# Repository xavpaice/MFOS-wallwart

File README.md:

# MFOS-wallwart

Slightly updated MFOS wallwart power supply for Eurorack, adding a +5V rail.

V0.1 dev version

This schematic and PCB is written using Kicad, v6.0.2

For the original circuit, see http://musicfromouterspace.com/analogsynth_new/WALLWARTSUPPLY/WALLWARTSUPPLY.php.

Though I have used insanely thick traces, the actual rating of the circuit with
stated components is about 1A total.  If you need more, consider something more
expensive.

The information in this repository is provided in good faith but no
responsibility is accepted for the accuracy or suitability for any purpose; you
use it entirely at your own risk.

Please report errors and omissions at
https://github.com/xavpaice/MFOS-wallwart/issues.

Misuse of electronics can result in nasty things like death, or, worse, fried
Eurorack modules.  Please take care.  Remember to only chew on lead free diodes.

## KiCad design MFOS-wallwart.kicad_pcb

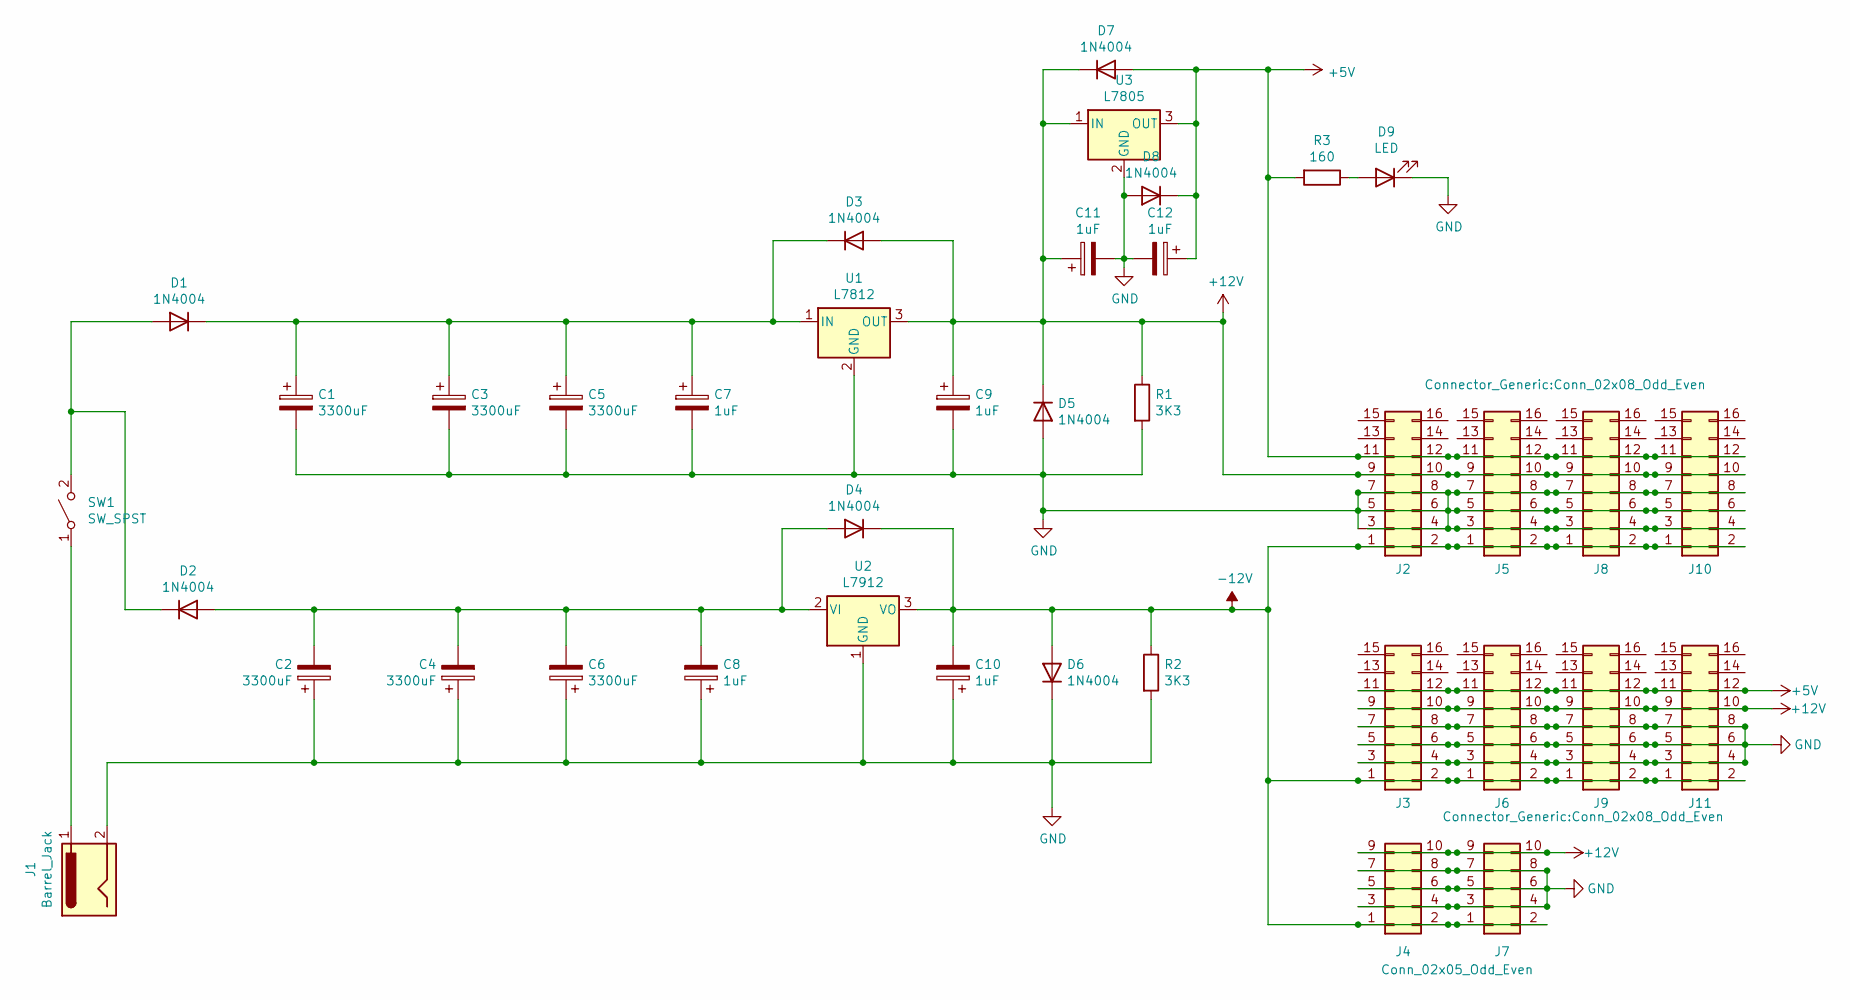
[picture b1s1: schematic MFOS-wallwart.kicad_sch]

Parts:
C1, C2, C3, C4, C5, C6: 3300uF; CP_Radial_D18.0mm_P7.50mm
C7, C8, C9, C10, C11, C12: 1uF; CP_Radial_D6.3mm_P2.50mm
D1, D2, D3, D4, D5, D6, D7, D8: 1N4004; D_DO-41_SOD81_P10.16mm_Horizontal
D9: LED; PinHeader_1x02_P2.54mm_Vertical
J1: Barrel_Jack; PinHeader_1x02_P2.54mm_Vertical
J2, J3, J5, J6, J8, J9, J10, J11: Connector_Generic:Conn_02x08_Odd_Even; IDC-Header_2x08_P2.54mm_Vertical
J4, J7: Conn_02x05_Odd_Even; PinHeader_2x05_P2.54mm_Vertical
R1, R2: 3K3; R_Axial_DIN0207_L6.3mm_D2.5mm_P10.16mm_Horizontal
R3: 160; R_Axial_DIN0207_L6.3mm_D2.5mm_P10.16mm_Horizontal
SW1: SW_SPST; PinHeader_1x02_P2.54mm_Vertical
U1: L7812; TO-220-3_Vertical
U2: L7912; TO-220-3_Vertical
U3: L7805; TO-220-3_Vertical

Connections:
+5V: C12.1, D7.2 (A), D8.1 (K), J2.11, J2.12, J3.11, J3.12, J5.11, J5.12, J6.11, J6.12, J8.11, J8.12, J9.11, J9.12, J10.11, J10.12, J11.11, J11.12, R3.2, U3.3 (OUT)
+12V: C9.1, C11.1, D3.2 (A), D5.1 (K), D7.1 (K), J2.9, J2.10, J3.9, J3.10, J4.9, J4.10, J5.9, J5.10, J6.9, J6.10, J7.9, J7.10, J8.9, J8.10, J9.9, J9.10, J10.9, J10.10, J11.9, J11.10, R1.1, U1.3 (OUT), U3.1 (IN)
-12V: C10.2, D4.1 (K), D6.2 (A), J2.1, J2.2, J3.1, J3.2, J4.1, J4.2, J5.1, J5.2, J6.1, J6.2, J7.1, J7.2, J8.1, J8.2, J9.1, J9.2, J10.1, J10.2, J11.1, J11.2, R2.1, U2.3 (VO)
GND: C1.2, C2.1, C3.2, C4.1, C5.2, C6.1, C7.2, C8.1, C9.2, C10.1, C11.2, C12.2, D5.2 (A), D6.1 (K), D8.2 (A), D9.1 (K), J1.2, J2.3, J2.4, J2.5, J2.6, J2.7, J2.8, J3.3, J3.4, J3.5, J3.6, J3.7, J3.8, J4.3, J4.4, J4.5, J4.6, J4.7, J4.8, J5.3, J5.4, J5.5, J5.6, J5.7, J5.8, J6.3, J6.4, J6.5, J6.6, J6.7, J6.8, J7.3, J7.4, J7.5, J7.6, J7.7, J7.8, J8.3, J8.4, J8.5, J8.6, J8.7, J8.8, J9.3, J9.4, J9.5, J9.6, J9.7, J9.8, J10.3, J10.4, J10.5, J10.6, J10.7, J10.8, J11.3, J11.4, J11.5, J11.6, J11.7, J11.8, R1.2, R2.2, U1.2 (GND), U2.1 (GND), U3.2 (GND)
unnamed: C1.1, C3.1, C5.1, C7.1, D1.1 (K), D3.1 (K), U1.1 (IN)
unnamed: C2.2, C4.2, C6.2, C8.2, D2.2 (A), D4.2 (A), U2.2 (VI)
unnamed: D1.2 (A), D2.1 (K), SW1.2 (B)
unnamed: D9.2 (A), R3.1
unnamed: J1.1, SW1.1 (A)

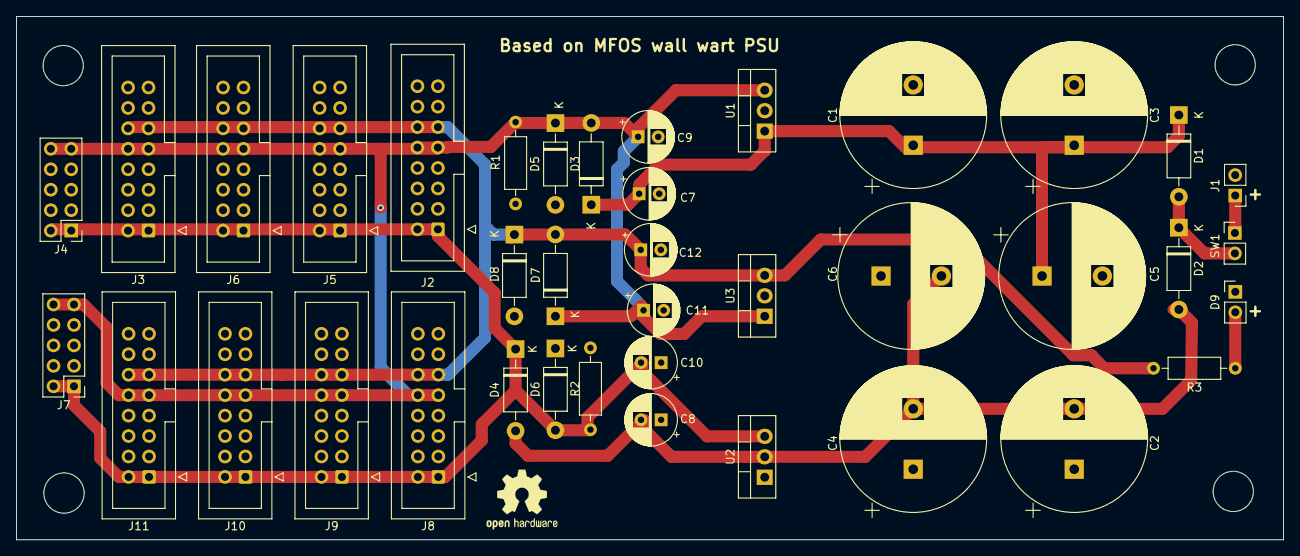
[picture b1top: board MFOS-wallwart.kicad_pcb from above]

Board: 2 copper layers, 157.4 x 65.0 mm, 39 parts (0 on the bottom side), 9 nets.

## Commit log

2021-02-08 add README
2021-03-12 Updated for extra outputs
2023-05-13 Minor updates, add polarity to 1uf caps
